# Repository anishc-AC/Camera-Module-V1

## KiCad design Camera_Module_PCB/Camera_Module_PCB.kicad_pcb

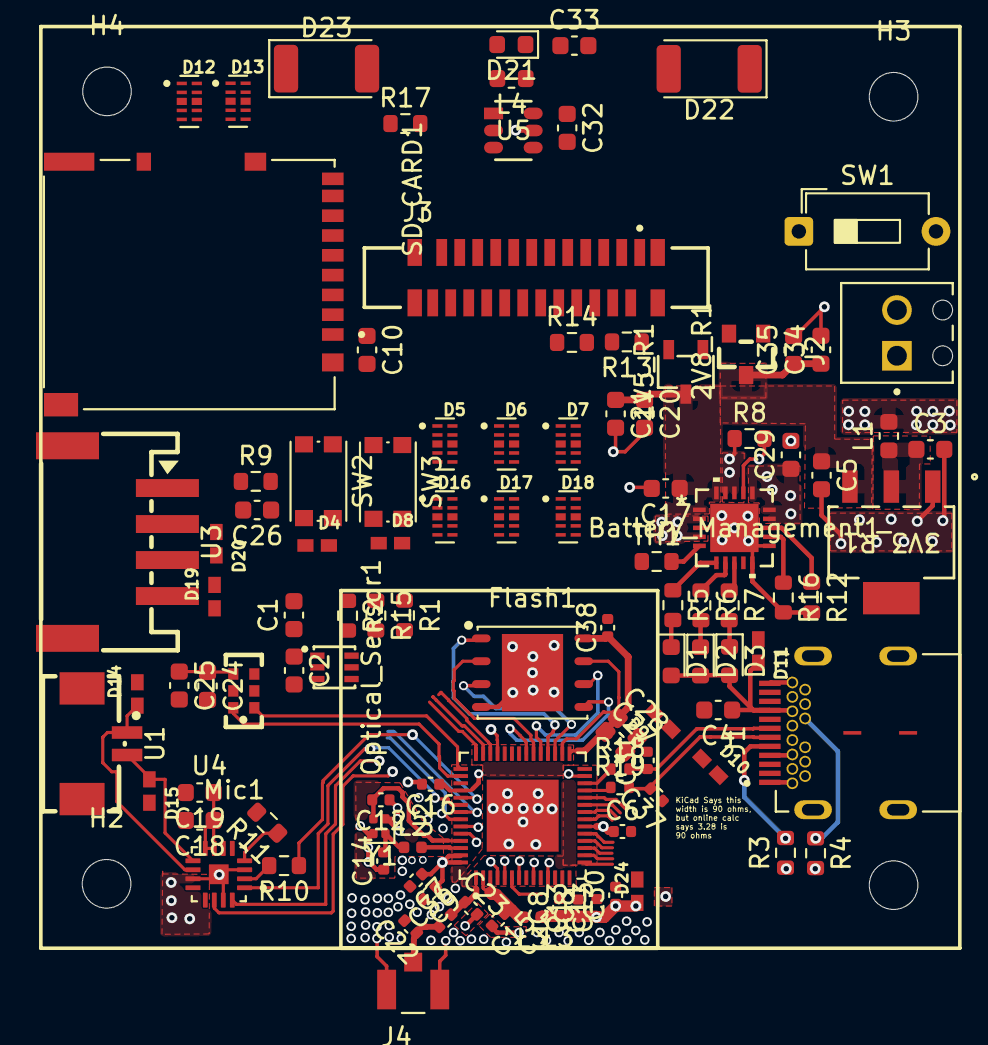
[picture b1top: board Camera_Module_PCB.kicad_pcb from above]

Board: 4 copper layers, 111 parts (0 on the bottom side), 78 nets.

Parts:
1V5_R1: ME6206A15XG; SOT-23-3_L2.9-W1.6-P1.90-LS2.8-BR
2V8_R1: ME6206A28XG; SOT-23_L2.9-W1.3-P1.90-LS2.4-BR
3V3_R1: LM1117MPX-33NOPB; SOT223-318H_OSI
Battery_Management1: MCP73871T-4CCI/ML; QFN20_4x4MC_MCH
C1, C19, C24, C32: 10uF; C_0603_1608Metric
C2, C4, C10, C18, C28: 0.1uF; C_0603_1608Metric
C3, C5: 10 uF; C_0603_1608Metric
C6, C7, C11, C16: 0.1uF; C_0402_1005Metric
C8, C9, C30, C38: 10uF; C_0402_1005Metric
C12, C14: 15pF; C_0402_1005Metric
C13: 1uF; C_0402_1005Metric
C15: .1uF; C_0402_1005Metric
C17: 4.7uF; C_0603_1608Metric
C20, C34: 1 uF; C_0603_1608Metric
C21, C35: 100 nF; C_0603_1608Metric
C22, C31, C37: NC; C_0402_1005Metric
C23: 1.8pF; C_0402_1005Metric
C25, C26: 100nF; C_0603_1608Metric
C27, C33: 1uF; C_0603_1608Metric
C29: 4.7u; C_0603_1608Metric
C36: 1pF; C_0402_1005Metric
D1, D2, D3: LED; LED_0603_1608Metric
D4, D8, D9, D10, D11, D14, D15, D19, D20, D24: 0402ESDA-MLP1; ESD_0402ESDA-MLP1
D5, D6, D7, D12, D13, D16, D17, D18: TPD4E02B04DQAR; DIO_TPD4E02B04DQAR
D21: D_Zener; D_0603_1608Metric
D22, D23: LED; LED_2010_5025Metric
Flash1: W25Q128JVPIQ
H1, H2, H3, H4: MountingHole; MountingHole_2.7mm
J1: SS-52400-002; BELFUSE_SS-52400-002
J2: Conn_01x02; PHOENIX_1725656
J3: FFC2A32-24-T; GCT_FFC2A32-24-T
J4: U.FL-R-SMT-1_80_; HIROSE_U.FL-R-SMT-1_80_
L1: 1uH; L_0603_1608Metric
L2: 15nH; L_0402_1005Metric
L3: 2nH; L_0402_1005Metric
L4: 6.8u; L_0603_1608Metric
Mic1: MSM261DGT003; MIC-SMD_6P-L4.0-W2.0_LMD4020T261-OC3
Optical_Sensor1: LTR-308ALS-01; SENSOR-SMD_6P-L2.0-W2.0-P0.65-BL
R1, R2, R9, R15: 10K; R_0603_1608Metric
R3, R4, R13, R14: 5.1k; R_0603_1608Metric
R5, R6, R7: 1K; R_0603_1608Metric
R8: 10k; R_0603_1608Metric
R10, R11: 100K; R_0603_1608Metric
R12: 1k; R_0603_1608Metric
R16: 25k; R_0603_1608Metric
R17: 10; R_0603_1608Metric
R18, R19: 22; R_0402_1005Metric
SD_CARD1: DM3AT-SF-PEJM5; HRS_DM3AT-SF-PEJM5
SW1: SW_DIP_x01; SW_DIP_SPSTx01_Slide_6.7x4.1mm_W7.62mm_P2.54mm_LowProfile
SW2, SW3: SW_Push; SW_Push_1P1T_NO_CK_KMR2
TH1: 10k; R_0603_1608Metric
U1: CONN-SMD_2P-P1.25_XUNPU_WAFER-MX1.25-2PWB
U2: ESP32-S3R8; QFN40P700X700X90-57N
U3: CONN-SMD_4P-P2.00_BX-PH-2.0-4PWT
U4: MAX98357AETE_T; QFN50P300X300X80-17N
U5: AP3032KTR-G1; SOT23-6_DIO
Y1: Q40,0-JXS10-8-10/10-FU-LF1; Crystal_SMD_1210-4Pin_1.2x1.0mm

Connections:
+3.3V: C1.1, C2.1, C6.1, C7.1, C8.1, C9.1, C10.1, C11.1, C13.1, C16.1, C18.1, C19.1, C24.1, C25.1, C30.1, C32.1, D24.1, L1.2, L3.1, L4.1, Mic1.1 (VDD), Optical_Sensor1.1 (VDD), R1.1, R2.1, R9.1, R11.2, R15.1, SD_CARD1.4 (VDD), U2.20 (VDD3P3_RTC), U2.46 (VDD3P3_CPU), U2.55 (VDDA1), U2.56 (VDDA2), U3.1, U4.7 (VDD), U4.8 (VDD), U5.6 (VIN)
/BCLK: U2.51 (GPIO45), U4.16 (BCLK)
/BOOT: D8.1, SW3.2, U2.5 (GPIO0)
/Din: U2.48 (MTMS), U4.1 (DIN)
/Gain: R10.1, U2.47 (MTDI)
/HSYNC: D5.1 (IO1), D5.2 (IO2), J3.9 (HSYNC), U2.7 (GPIO2)
/LED_CT: U2.40 (GPIO35), U5.4 (CTRL)
/LNA_IN: C23.1, C36.2, U2.1 (LNA_IN)
/LRCLK: U2.52 (GPIO46), U4.14 (LRCLK)
/Light_INT: Optical_Sensor1.5 (INT), R15.2, U2.39 (GPIO34)
/MISO: D13.1 (IO1), D13.2 (IO2), SD_CARD1.7 (DAT0), U2.18 (GPIO13)
/MOSI: D12.1 (IO1), D12.2 (IO2), SD_CARD1.3 (CMD), U2.16 (GPIO11)
/OV: C33.1, D21.1 (K), D22.2 (A), U5.5 (OV)
/PCLK: D6.1 (IO1), D6.2 (IO2), J3.17 (PCLK), U2.21 (XTAL_32K_P)
/PDM_CLK: Mic1.4 (CLK), U2.43 (GPIO38)
/PDM_DATA: Mic1.3 (DATA), U2.44 (MTCK)
/Power Supply/5V_USB: Battery_Management1.2 (VPCC), Battery_Management1.4 (PROG2), Battery_Management1.18 (IN), Battery_Management1.19 (IN), C4.1, D1.2 (A), D2.2 (A), D3.2 (A), D11.2, J1.A4 (VBUSA1), J1.A9 (VBUSA2), J1.B4 (VBUSB1), J1.B9 (VBUSB2), R8.1
/Power Supply/CHG_EN: Battery_Management1.17 (CE), R8.2, SW1.1
/Power Supply/VBAT: Battery_Management1.14 (VBAT), Battery_Management1.15 (VBAT), Battery_Management1.16 (VBAT_SENSE), C29.1, J2.1
/RST: C26.1, D4.1, R9.2, SW2.2, U2.4 (CHIP_PU)
/SCL: J3.5 (SCL), Optical_Sensor1.4 (SCL), R1.2, U2.42 (GPIO37)
/SCLK: D13.4 (IO3), D13.5 (IO4)
/SDA: J3.3 (SDA), Optical_Sensor1.6 (SDA), R2.2, U2.41 (GPIO36)
/SD_CLK: SD_CARD1.5 (CLK), U2.17 (GPIO12)
/SD_CS: D12.4 (IO3), D12.5 (IO4), SD_CARD1.2 (CD/DAT3), U2.15 (GPIO10)
/SPICLK: Flash1.6 (CLK), U2.33 (SPICLK)
/SPIHD: Flash1.7 (HOLD/RESET(IO3)), U2.30 (SPIHD)
/SPIWP: Flash1.3 (/WP(IO2)), U2.31 (SPIWP)
/USB_D+: C37.2, D10.1, J1.A6 (DP1), J1.B6 (DP2), R19.2
/USB_D-: C31.1, D9.1, J1.A7 (DN1), J1.B7 (DN2), R18.2
/VDD_SPI: C27.1, C28.1, C38.1, Flash1.8 (VCC), U2.29 (VDD_SPI)
/VSYNC: D5.4 (IO3), D5.5 (IO4), J3.7 (VSYNC), U2.6 (GPIO1)
/XMCLK: D6.4 (IO3), D6.5 (IO4), J3.13 (MLCK), U2.10 (GPIO5)
/XTAL_N: C12.2, U2.53 (XTAL_N), Y1.3 (Output)
/XTAL_P: L2.2, U2.54 (XTAL_P)
/Y2: D7.1 (IO1), D7.2 (IO2), J3.19 (Y2), U2.22 (XTAL_32K_N)
/Y3: D7.4 (IO3), D7.5 (IO4), J3.21 (Y3), U2.24 (GPIO18)
/Y4: D16.1 (IO1), D16.2 (IO2), J3.22 (Y4), U2.27 (GPIO21)
/Y5: D16.4 (IO3), D16.5 (IO4), J3.20 (Y5), U2.23 (GPIO17)
/Y6: D17.1 (IO1), D17.2 (IO2), J3.18 (Y6), U2.19 (GPIO14)
/Y7: D17.4 (IO3), D17.5 (IO4), J3.16 (Y7), U2.12 (GPIO7)
/Y8: D18.1 (IO1), D18.2 (IO2), J3.14 (Y8), U2.11 (GPIO6)
/Y9: D18.4 (IO3), D18.5 (IO4), J3.12 (Y9), U2.9 (GPIO4)
AVDD_2V8: 2V8_R1.2 (VOUT), J3.4 (AVDD), J3.11 (DOVDD), R13.1
GND: 1V5_R1.1 (VSS), 2V8_R1.1 (VSS), 3V3_R1.1 (ADJUST/GROUND), Battery_Management1.3 (SEL), Battery_Management1.10 (VSS), Battery_Management1.11 (VSS), Battery_Management1.21 (EP), C1.2, C2.2, C3.2, C4.2, C5.2, C6.2, C7.2, C8.2, C9.2, C10.2, C11.2, C12.1, C13.2, C14.1, C15.2, C16.2, C17.2, C18.2, C19.2, C20.2, C21.2, C22.2, C23.2, C24.2, C25.2, C26.2, C27.2, C28.2, C29.2, C30.2, C31.2, C32.2, C33.2, C34.2, C35.2, C37.1, C38.2, D4.2, D5.3 (GND), D5.8 (GND), D6.3 (GND), D6.8 (GND), D7.3 (GND), D7.8 (GND), D8.2, D9.2, D10.2, D11.1, D12.3 (GND), D12.8 (GND), D13.3 (GND), D13.8 (GND), D14.2, D15.2, D16.3 (GND), D16.8 (GND), D17.3 (GND), D17.8 (GND), D18.3 (GND), D18.8 (GND), D19.1, D20.1, D24.2, Flash1.4 (GND), Flash1.9 (GND), J1.A1 (GNDA1), J1.A12 (GNDA2), J1.B1 (GNDB1), J1.B12 (GNDB2), J1.G1 (GND/SHIELD), J2.2, J3.2 (AGND), J3.15 (GND), J3.S1 (SHIELD), J3.S2 (SHIELD), J3.S3 (SHIELD), J3.S4 (SHIELD), J4.G1, J4.G2, Mic1.2 (GND), Mic1.5 (GND), Mic1.6 (L/R), Optical_Sensor1.3 (GND), R3.1, R4.2, R12.2, R14.1, R16.2, R17.2, SD_CARD1.6 (VSS), SD_CARD1.P1 (SHIELD), SD_CARD1.P2 (SHIELD__1), SD_CARD1.P3 (SHIELD__2), SD_CARD1.P4 (SHIELD__3), SW1.2, SW2.1, SW3.1, TH1.1, U2.57 (GND), U3.2, U4.3 (GND), U4.11 (GND), U4.15 (GND), U4.17 (EP), U5.2 (GND), Y1.2 (Ground), Y1.4 (Ground)
unnamed: 3V3_R1.2 (OUTPUT), C3.1, L1.1
unnamed: Battery_Management1.6 (*PG), R5.1
unnamed: Battery_Management1.13 (PROG1), R12.1
unnamed: Battery_Management1.12 (PROG3), R16.1
unnamed: Battery_Management1.8 (STAT1/*LBO), R7.1
unnamed: Battery_Management1.7 (STAT2), R6.1
unnamed: Battery_Management1.5 (THERM), TH1.2
unnamed: C22.1, C36.1, J4.SIG
unnamed: D1.1 (K), R5.2
unnamed: D2.1 (K), R6.2
unnamed: D3.1 (K), R7.2
unnamed: D21.2 (A), L4.2, U5.1 (SW)
unnamed: D22.1 (K), D23.2 (A)
unnamed: D23.1 (K), R17.1, U5.3 (FB)
unnamed: Flash1.1 (CS), U2.32 (SPICS0)
unnamed: Flash1.5 (DI(IO0)), U2.35 (SPID)
unnamed: Flash1.2 (DO(IO1)), U2.34 (SPIQ)
unnamed: J1.A5 (CC1), R3.2
unnamed: J1.B5 (CC2), R4.1
unnamed: J3.8 (PWDN), R14.2
unnamed: J3.6 (RST), R13.2
unnamed: R19.1, U2.25 (GPIO19)
unnamed: R18.1, U2.26 (GPIO20)
unnamed: D20.2, U2.50 (U0RXD), U3.3
unnamed: D19.2, U2.49 (U0TXD), U3.4
unnamed: R10.2, U4.2 (GAIN_SLOT)
unnamed: D14.1, U1.1, U4.10 (OUTN)
unnamed: D15.1, U1.2, U4.9 (OUTP)
unnamed: R11.1, U4.4 (SD_MODE)
unnamed: C14.2, L2.1, Y1.1 (Input)
VDD3P3: C15.1, L3.2, U2.2 (VDD3P3), U2.3 (VDD3P3)
VDD_1V5: 1V5_R1.2 (VOUT), J3.10 (DVDD)
V_OUT_BM: 1V5_R1.3 (VIN), 2V8_R1.3 (VIN), 3V3_R1.3 (INPUT), Battery_Management1.1 (OUT), Battery_Management1.20 (OUT), C5.1, C17.1, C20.1, C21.1, C34.1, C35.1

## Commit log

2026-01-14 Added KiCad 9.0 Projects
2026-01-15 Added Multiple Component CAD Models
    Added CAD models for the ESP32-S3, a USB C connector, a SD Card Slot, and an FPC Connector
2026-01-17 Added Extra CAD Models for Voltage
2026-01-18 Moved Power Related Components to a new sheet
2026-01-18 Fixed an Error with added sheet name
2026-01-18 Updated some elements of the schematic
2026-01-21 Modified the power supply and organized folders
2026-01-24 Made some new connections on the charging module
2026-01-26 Quick Refresh
2026-01-26 Small Additions to Charger
2026-01-27 Made more small changes to the schematic
2026-01-28 Made some small additions and notes
2026-01-30 Added three new components
2026-01-31 Added components and began connections
2026-02-03 ESP32 Modified
    -Changed ESP32 to ESP32R8
    -Changed ESP32 Filtering
    -Can you simulate the VDDA output?
2026-02-04 Added more minor circuits w/ notes
2026-02-07 Made connections to FPC Connector
    I connected the MCU pins to the FPC connector for the camera module. There is still power missing for the FPC connector for 2.8V and 1.5V. We still need to wire some pins to ESD protection ICs, shoul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
2026-02-10 Rerouted Multiple Networks & Wired Speaker
    Power supplies to the ESP32 were rerouted to fit the recommended set-up. The MAX98357 speaker amp was wired and analyzed to understand function. Multiple inputs to the FPC connector to the camera mod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
2026-02-11 Added most of the remaining components
    Added the microphone, two LDO regulators, light sensor, and LED driver. The missing components will be passive elements and specific infared LEDs for the LED driver.
2026-02-11 Added the CAD models of the components
2026-02-16 Minor Changes
    Minor Chanhes
2026-02-17 Finished Most Component connections
    Finished the connections for the microphone, the FPC connector, and the LED driver. Comments were added to describe the current design. LED driver needs calculations to determine passive element valu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
2026-02-18 Minor Changes
2026-02-18 V1.1.0
    Preliminary Schematic needs a couple of changes left to be made.
2026-02-18 Made Minor Changes and Reviewed Schematic
    Only a few more connections must be made to the ESP32 component. All other components should be complete.
2026-02-22 Compiled Footprints and Set up PCB layout
    All of the footprints that correspond to the schematic symbols were properly referenced in the schematic annotations. The PCB layout was then updated to contain all of the appropriate footprints. Fin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
2026-02-23 Began early Layout for PCB
    Moved most of the ICs into a general area layout for the PCB.
2026-02-24 Finished Schematic Except for a small few passives
    Finished all of the connections in the schematic page and added a new LED driver. A small selection of passive elements must be given proper values after some calculations.
2026-02-26 Made minor changes to schematic
    Schematic is finished except for the inclusion of an RF antenna for Pin 1 of the ESP32. Waiting on team confirmation about its inclusion.
2026-03-03 Added Most ICs to the General PCB Layout
    Most of the intended ICs that are going to be used were put into a general IC layout. A decision will need to be made in regards to the antenna. The ESP32 Model that is being used may be replaced, or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
    Once the decision is made, more can be added.
2026-03-05 MCU Layout Started
    The layout for the ESP32 has been started, according to the recommended 4-Layer layout. Please look over the antenna and continue layout.
2026-03-06 Made a small comment about LEDs
    Made a comment about LEDs. We need to give out LEDs and Diodes a specific part number (usually from Digikey).
2026-03-11 Continued to map out ESP32 Module portion of PCB
    Continued to follow the Espressif PCB layout by routing power and placing general component location. The quartz crystal footprint was changed and the model we will be using replaced the value of the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
2026-03-14 Made some schematic edits & continued work on layout
    Made some minor adjustments for the schematic to prepare for review. The layout continues to be built.
2026-03-16 Routed Antenna and Crystal
    The antenna and crystals that connect to the ESP32-S3 were routed and a dense layer of ground vias were used for isolation along with no net filled zones. There is a small concern between the RF trac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
2026-03-29 Continued Routing of ESP32 chip and USB
    Continued to create general layouts for the necessary ESP32 chip and power suuply
2026-04-04 Finished Power Supply
    The power supply was finished for the ESP32 Chip and the board as a whole. A large plain was constructed in the third layer of the PCB to hold the 3.3V power supply from the regulator. Multiple trace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
2026-04-10 Continued General Component Layout
    More components were placed in general areas where they are predicted to remain. The two LDO voltage regulators for the camera power supply were connected to the main output voltage of the battery ma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
2026-04-13 Finished General Layout
    All components have their general location on the PCB with some wiggle room for most parts to move around. Traces are what is left to complete the board.
2026-05-01 Began routing remaining paths
    Routed the paths that connect the ESP32 chip and the amplifier IC that is used for the speaker. A large zone for the 3.3V power was created in the power plane to allow for power to be routed througho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
